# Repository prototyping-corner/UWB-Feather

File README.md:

# UWB Feather

The Ultra-WideBand Feather incorporates the Decawave DWM1000 module and an ATSAMD21 ARM Cortex M0 into the Adafruit feather form-factor. The DWM1000 module is an IEEE802.15.4-2011 UWB compliant wireless module capable of precision indoor positioning and high data rates, making this board perfect for robotics projects where localization is required.  

For full project details and documentation visit [prototypingcorner.io/projects/uwb-feather](prototypingcorner.io/projects/uwb-feather).

## Hardware
Licensed under the CERN OHL v1.2.  

## Firmware
Firmware providing in this repository is for testing the DWM1000 module and utilizes the [thotro/arduino-dw1000](https://github.com/thotro/arduino-dw1000) library. As this repository is no longer actively maintained, future development will focus on a new library.

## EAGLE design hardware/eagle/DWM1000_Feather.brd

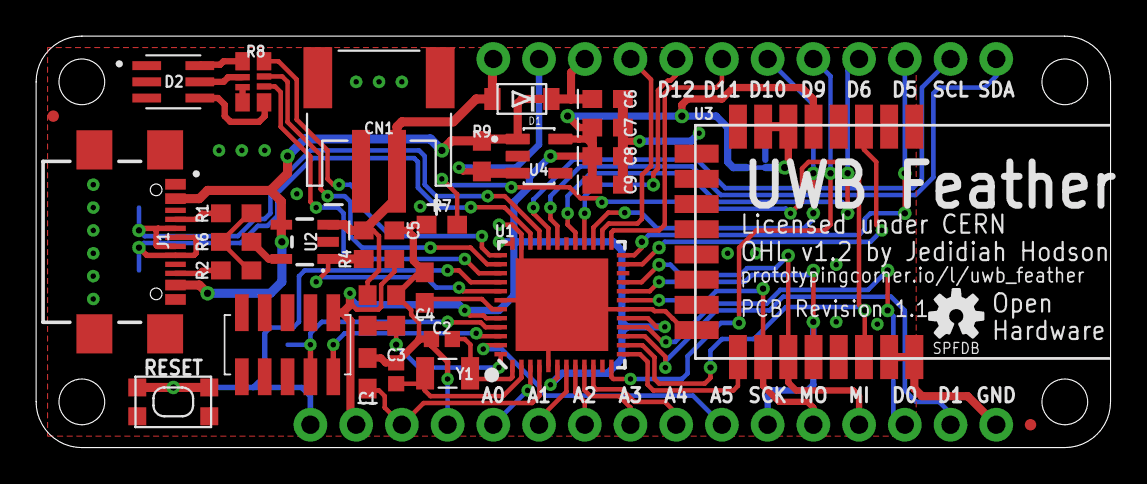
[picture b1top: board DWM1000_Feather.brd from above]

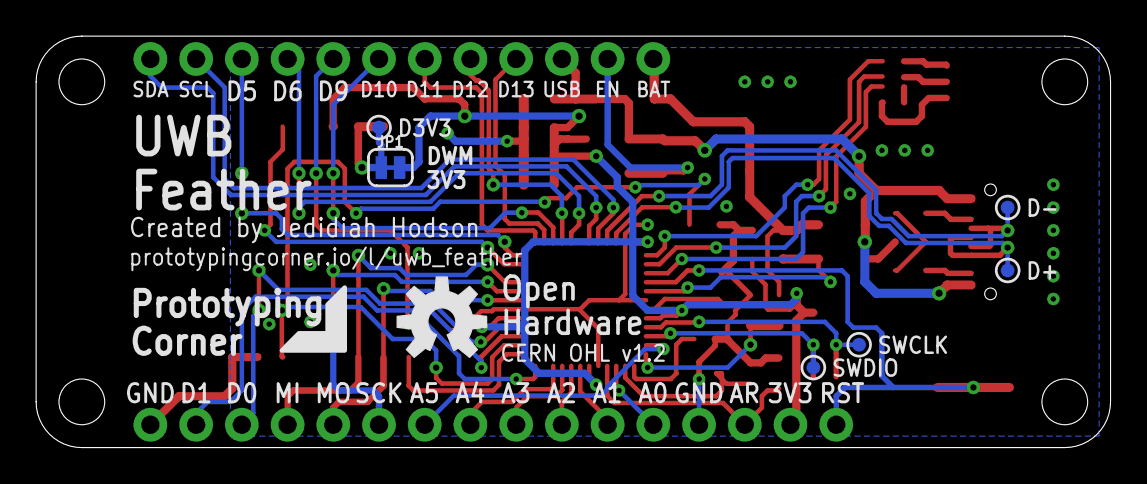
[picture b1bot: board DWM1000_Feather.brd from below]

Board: 2 copper layers, 59.7 x 22.9 mm, 41 parts (7 on the bottom side), 50 nets.

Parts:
C1, C4, C6, C9: 1uF; 0603-POLAR
C2, C3: 15pF; 0402
C5, C7, C8: 10uF; 0603-POLAR
CN1: JST-PH-2-SMT-RA
D1: SOD-123FL
D2: ASMT-YTD7-0AA02; LED_ASMT-YTD7-0AA02
FD1, FD2: FIDUCIALUFIDUCIAL; FIDUCIAL-MICRO
J1: USB4110-GF-A; GCT_USB4110-GF-A
J2: 1X16_NO_SILK
J3: 1X12_NO_SILK
J4: 20021221-00010C4LF
JP1: DWM_3V3; SMT-JUMPER_2_NC_TRACE_SILK
LOGO1: OSHW-LOGOS; OSHW-LOGO-S
R1, R2, R4, R6: 5K1; 0603
R3, R5, R7, R9: 100K; 0603
R8: YC124-JR-07330RL; YAG_YC124
SW1: SPST_TACT-KMR2; KMR2
TP1, TP2, TP3, TP4, TP5: TEST-POINT3; PAD.03X.03
U1: ATSAMD21G-M; QFN-48
U2: MCP73832; SOT23-5
U3: DWM1000; XCVR_DWM1000
U4: AP2112K-3.3TRG1; SOT95P285X140-5N
U$2: OSHW-LOGO-M
Y1: FC-135_32.7680KA-A0; XTAL_FC-135_32.7680KA-A0

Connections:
3.3V: C7.+, C8.+, C9.+, J2.15, J4.1, JP1.2, R4.1, U1.6, U1.17, U1.36, U1.44, U3.5, U4.5
A0: J2.12, U1.3
A1: J2.11, U1.7
A2: J2.10, U1.8
A3: J2.9, U1.9
A4: J2.8, U1.10
A5: J2.7, U1.47
AREF: C1.+, J2.14, U1.4
BATT_S: R4.2, U1.41, U2.1
BATT_V: R3.2, R5.1, U1.48
D0: J2.3, U1.16
D1: J2.2, U1.15
D2: U1.23, U3.3
D3: R7.2, U1.14, U3.22
D4: U1.13, U3.17
D5: J3.3, U1.24
D6: J3.4, U1.29
D9: J3.5, U1.12
D10: J3.6, U1.27
D11: J3.7, U1.25
D12: J3.8, U1.28
D13: J3.9, U1.26
D+: J1.A6, J1.B6, TP1.P$1, U1.34
D-: J1.A7, J1.B7, TP2.P$1, U1.33
DWM_3V3: JP1.1, TP5.P$1, U3.6, U3.7
EN: J3.11, R9.2, U4.3
GND: C1.-, C2.1, C3.1, C4.-, C5.-, C6.-, C7.-, C8.-, C9.-, CN1.2, D2.1, D2.2, D2.3, J1.A1/B12, J1.B1/A12, J1.S1, J1.S2, J1.S3, J1.S4, J2.1, J2.13, J4.3, J4.5, J4.9, R1.1, R2.1, R5.2, R6.1, R7.1, SW1.1, SW1.3, U1.5, U1.18, U1.35, U1.42, U1.THERM_GND, U2.2, U3.8, U3.16, U3.21, U3.23, U3.24, U4.2
MISO: J2.4, U1.21, U3.19
MOSI: J2.5, U1.19, U3.18
unnamed: D2.6, R8.5
unnamed: D2.5, R8.6
unnamed: R8.7, R8.8
unnamed: D2.4, R8.1
unnamed: R6.2, U2.5
unnamed: J1.A5, R1.2
unnamed: J1.B5, R2.2
unnamed: C2.2, U1.1, Y1.1
unnamed: C4.+, U1.43
unnamed: C3.2, U1.2, Y1.2
RESET: J2.16, SW1.2, SW1.4, U1.40
RGB_B: R8.4, U1.37
RGB_G: R8.3, U1.38
RGB_R: R8.2, U1.39
SCK: J2.6, U1.20, U3.20
SCL: J3.2, U1.32
SDA: J3.1, U1.31
SWCLK: J4.4, TP4.P$1, U1.45
SWDIO: J4.2, TP3.P$1, U1.46
V_BATT: C5.+, CN1.1, D1.A, J3.12, R3.1, U2.3
V_USB: C6.+, D1.C, J1.A4/B9, J1.B4/A9, J3.10, R9.1, U2.4, U4.1

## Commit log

2019-12-29 Added CC BY-NC License
2019-12-29 Added parts BoM
2019-12-29 V1 Eagle CAD files
2019-12-29 Updated .gitignore
2019-12-29 Init platformio
2019-12-29 Added readme and media
2019-12-29 Anchor source code
2020-01-06 Version 1.1 update. BRD is INCOMPLETE
2020-01-07 Updated hardware license
2020-01-07 Updated for version 1.1
2020-01-07 Added board renders
2020-01-07 Updated U2 BoM item
2020-02-26 Lots of misc. changes

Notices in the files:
README.md:
License: CERN
hardware/eagle/DWM1000_Feather.brd:
Licensed under CERN
parts and their libraries:
SparkFun-Capacitors: Licensing: Creative Commons ShareAlike 4.0 International - https://creativecommons.org/licenses/by-sa/4.0
